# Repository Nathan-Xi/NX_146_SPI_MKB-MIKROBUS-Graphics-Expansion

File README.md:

# NX_146_SPI_MKB MIKROBUS™ Graphics Expansion Board

**Thank you for noticing this project.**:blush:

This is a graphics expansion board designed for all MIKROBUS™ supported development boards! (but you can still use it for other general-purpose applications as it's just a 4-SPI screen adapter board)

In **this** example SDK, I used an NXP FRDM-MCXA156 for demonstration.

## Parameters

**Display product name:** 鱼鹰光电DP146BT001-V12  
**Resolution:** 70×160  
**Display area size:** 1.46 inch  
**Touch:** capacitive  
**Screen IC:** NV3022  
**Touch panel IC:** CST08C  
**Interface:** 4-SPI (for display) & I2C (for touch panel)  
**ESD protection:** no  
**On-board external flash:** no  
**On-board cache:** no  

## Demos

### Demo 1: whiteboard

This demo turns the display into a whiteboard on which you can test the touch panel.✏️

The demo project (for MCUXpresso) was fully packed into a .zip called "whiteboard_demo.zip" (but of course you have to build and debug it by yourself)

### Demo 2: I3C temperature sensor data visualization

This demo is specific to the FRDM-MCXA156 development board.🔒

It uses the on-board MEMS temperature sensor (p3t1755) and reads it using the I3C bus.

## How to use the demos

The two demos are essential as they include the driver which the contributer had written (as this display acquires no existing driver).

If you want to port the driver to a new platform, please refer to Demo 1 as it included all you need for your custom project.

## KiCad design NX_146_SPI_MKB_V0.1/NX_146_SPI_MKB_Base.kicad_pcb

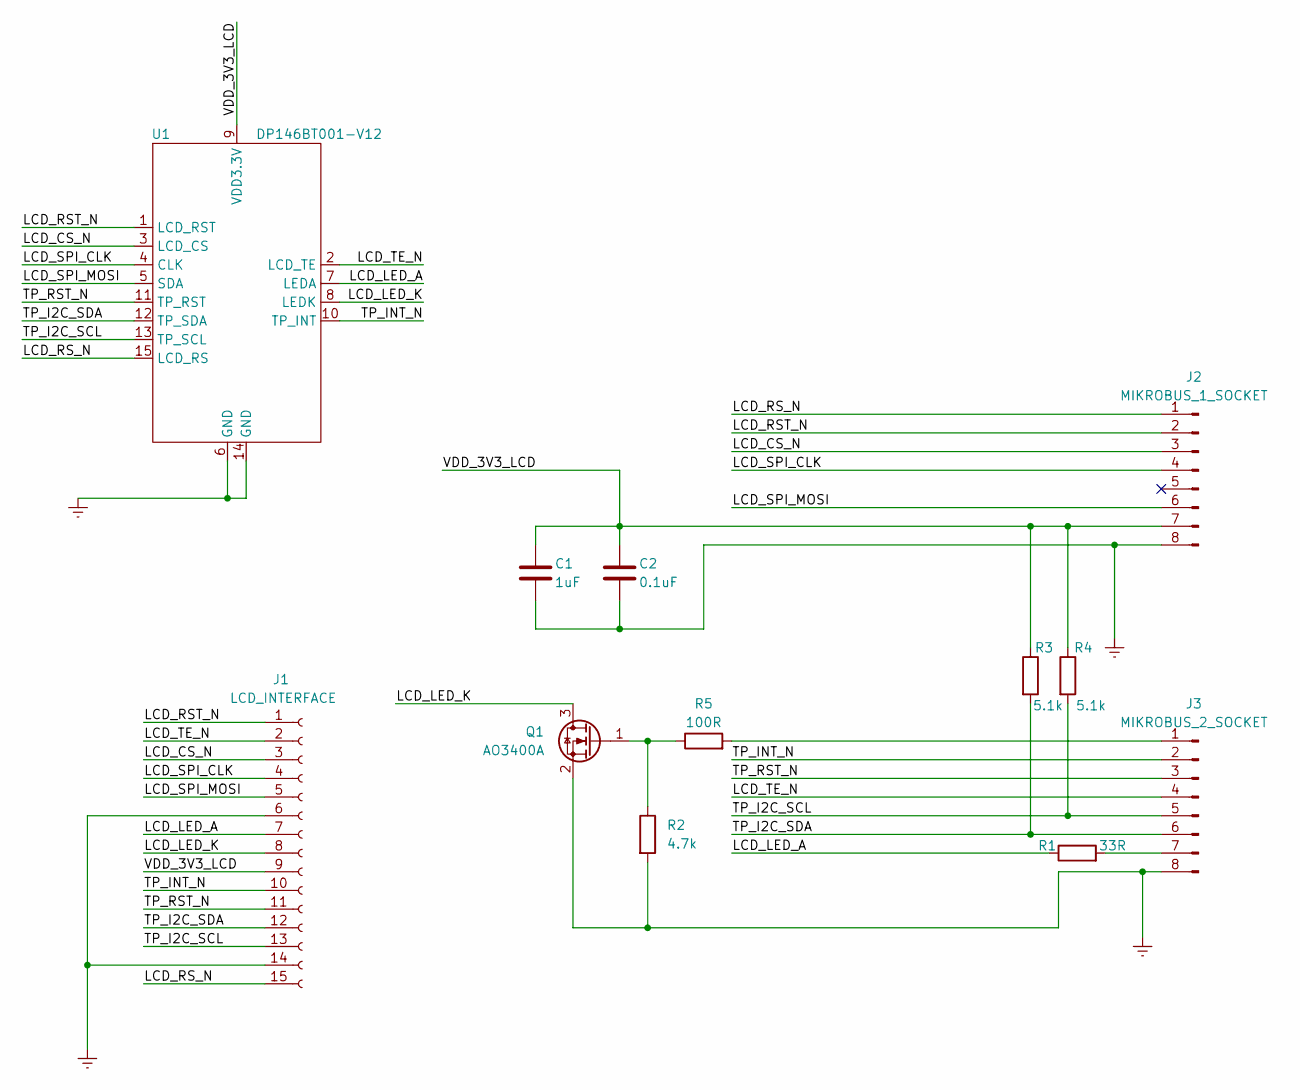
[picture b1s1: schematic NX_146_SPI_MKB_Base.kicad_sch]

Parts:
C1: 1uF; C_0402_1005Metric
C2: 0.1uF; C_0402_1005Metric
J1: LCD_INTERFACE; FPC-SMD_15P-P0.30_HDGC_.3K-HX-15PWB
J2: MIKROBUS_1_SOCKET; PinHeader_1x08_P2.54mm_Vertical
J3: MIKROBUS_2_SOCKET; PinHeader_1x08_P2.54mm_Vertical
Q1: AO3400A; SOT-23
R1: 33R; R_1206_3216Metric
R2: 4.7k; R_0402_1005Metric
R3, R4: 5.1k; R_0402_1005Metric
R5: 100R; R_0402_1005Metric
U1: DP146BT001-V12

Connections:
/LCD_CS_N: J1.3, J2.3, U1.3 (LCD_CS)
/LCD_LED_A: J1.7, R1.1, U1.7 (LEDA)
/LCD_LED_K: J1.8, Q1.3 (D), U1.8 (LEDK)
/LCD_RST_N: J1.1, J2.2, U1.1 (LCD_RST)
/LCD_RS_N: J1.15, J2.1, U1.15 (LCD_RS)
/LCD_SPI_CLK: J1.4, J2.4, U1.4 (CLK)
/LCD_SPI_MOSI: J1.5, J2.6, U1.5 (SDA)
/LCD_TE_N: J1.2, J3.4, U1.2 (LCD_TE)
/TP_I2C_SCL: J1.13, J3.5, R4.2, U1.13 (TP_SCL)
/TP_I2C_SDA: J1.12, J3.6, R3.2, U1.12 (TP_SDA)
/TP_INT_N: J1.10, J3.2, U1.10 (TP_INT)
/TP_RST_N: J1.11, J3.3, U1.11 (TP_RST)
/VDD_3V3_LCD: C1.1, C2.1, J1.9, J2.7, R3.1, R4.1, U1.9 (VDD3.3V)
Earth: C1.2, C2.2, J1.6, J1.14, J2.8, J3.8, Q1.2 (S), R2.2, U1.6 (GND), U1.14 (GND)
unnamed: J3.1, R5.2
unnamed: J3.7, R1.2
unnamed: Q1.1 (G), R2.1, R5.1

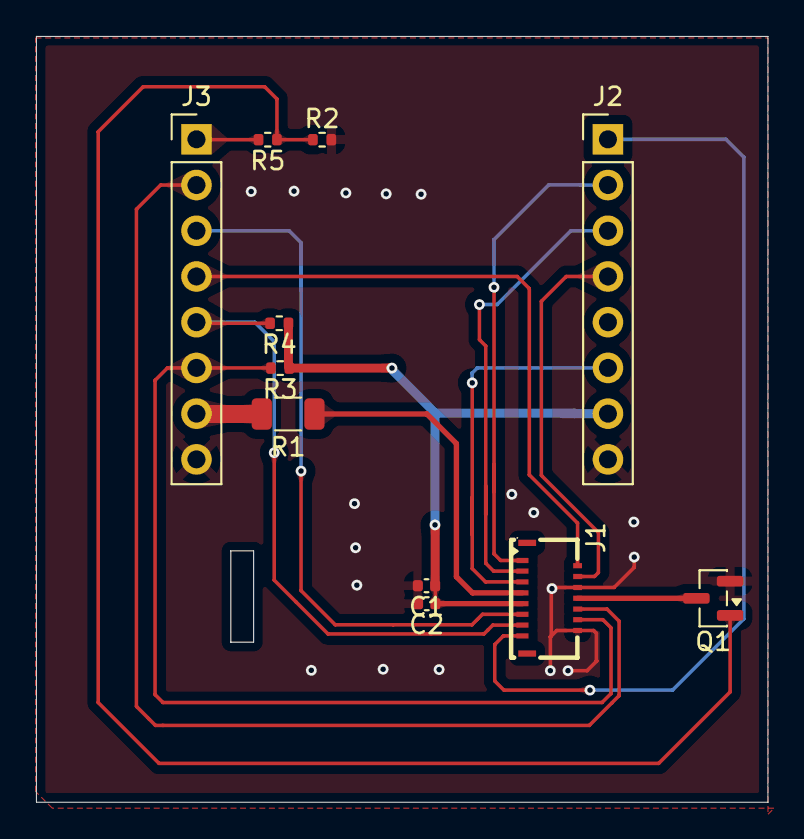
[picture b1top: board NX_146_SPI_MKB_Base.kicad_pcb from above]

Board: 4 copper layers, 40.6 x 42.5 mm, 11 parts (0 on the bottom side), 17 nets.

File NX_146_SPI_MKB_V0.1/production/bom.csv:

Designator,Footprint,Quantity,Value,LCSC Part #
C1,0402,1,1uF,
C2,0402,1,0.1uF,
J1,FPC-SMD_15P-P0.30_HDGC_.3K-HX-15PWB,1,LCD_INTERFACE,
J2,PinHeader_1x08_P2.54mm_Vertical,1,MIKROBUS_1_SOCKET,
J3,PinHeader_1x08_P2.54mm_Vertical,1,MIKROBUS_2_SOCKET,
Q1,SOT-23,1,AO3400A,
R1,1206,1,33R,
R2,0402,1,4.7k,
"R3, R4",0402,2,5.1k,
R5,0402,1,100R,
